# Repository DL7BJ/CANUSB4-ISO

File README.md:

CANUSB4-ISO 

Dieses Projekt basiert auf CANUSB4 vom MERG. Die Schaltung ist mit einer galvanischen Trennung zum USB Port erweitert. Der Code ist angepasst für MPLAB größer Version v6.25

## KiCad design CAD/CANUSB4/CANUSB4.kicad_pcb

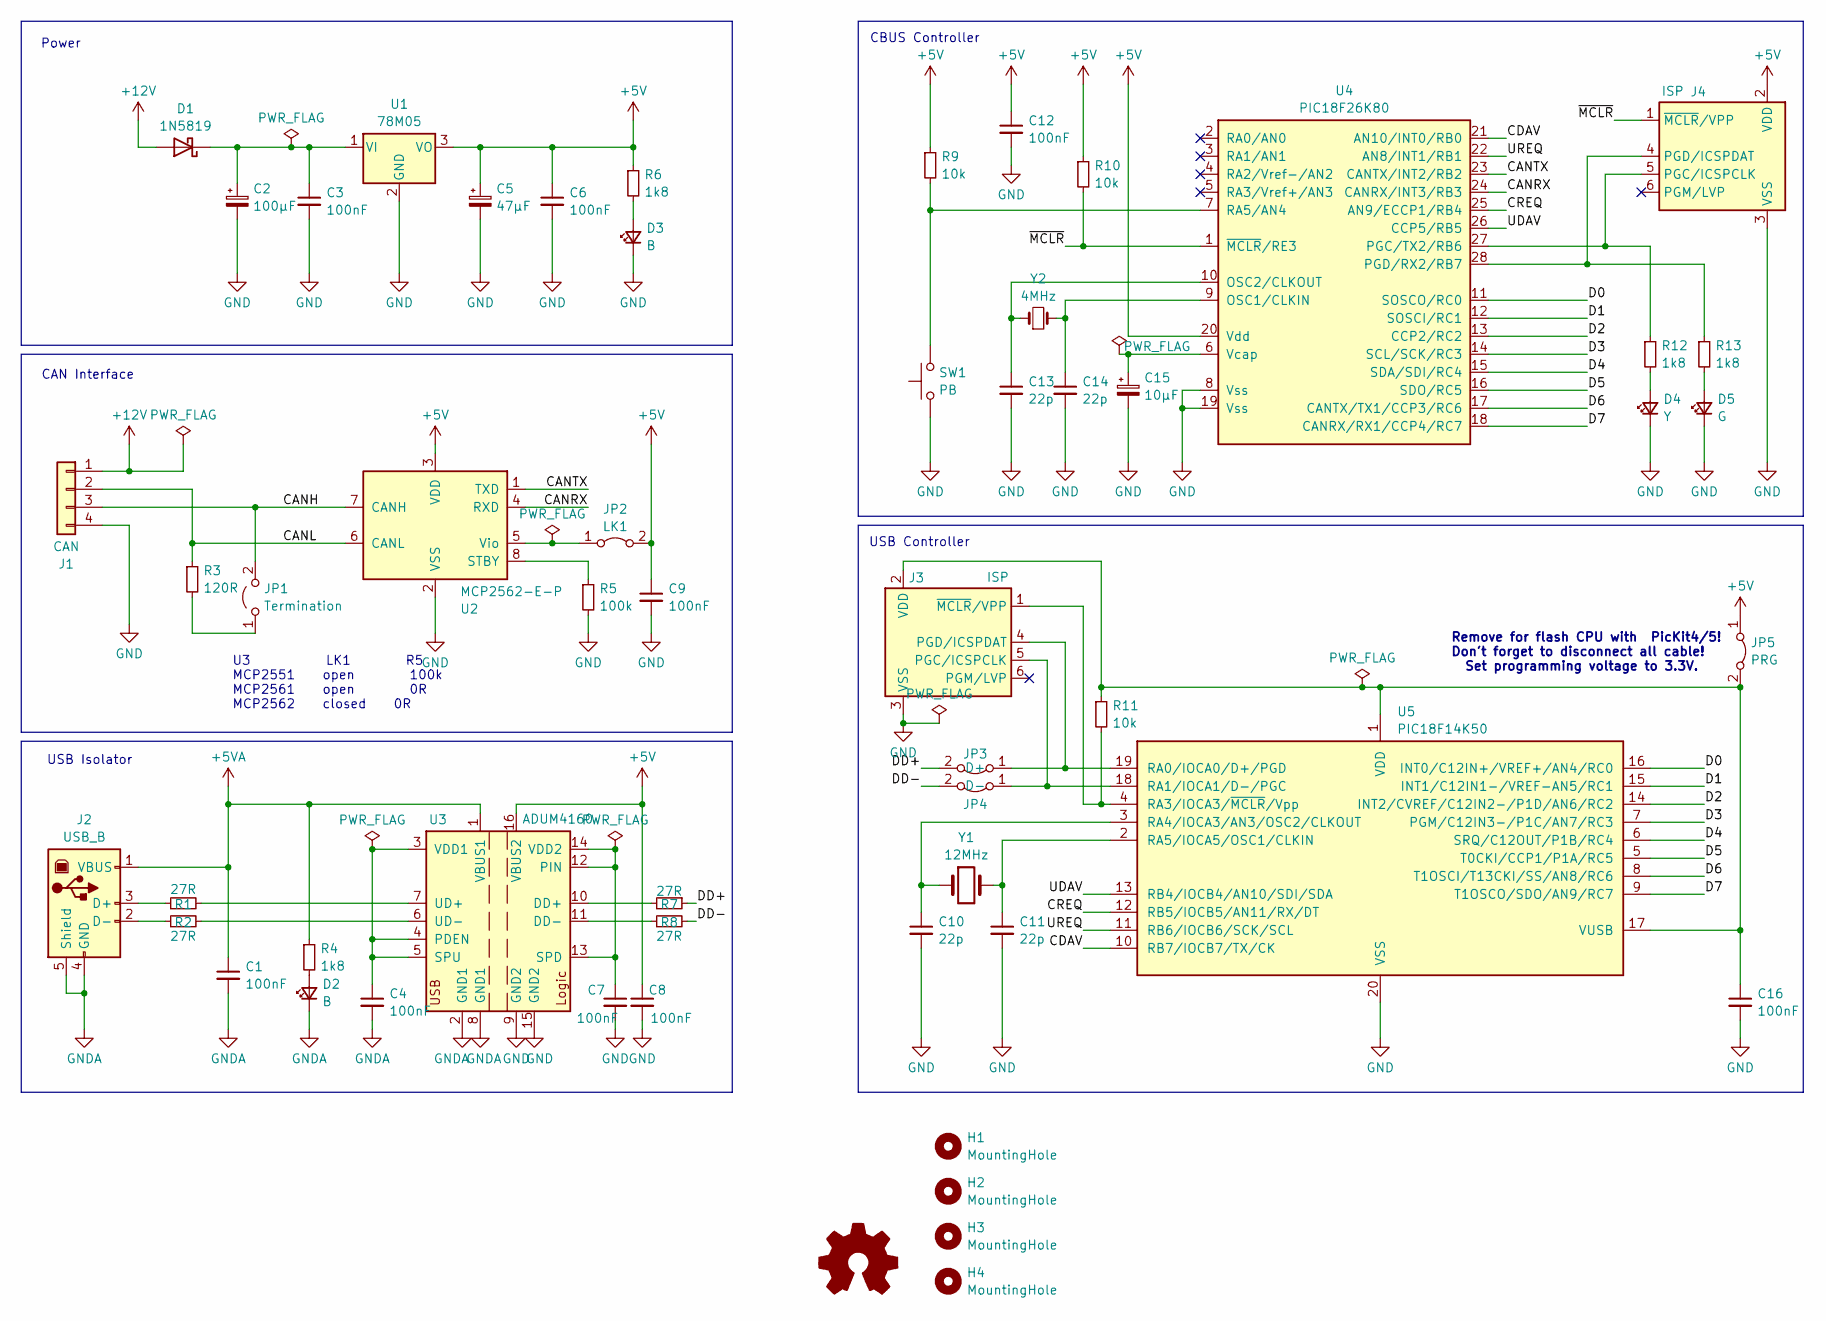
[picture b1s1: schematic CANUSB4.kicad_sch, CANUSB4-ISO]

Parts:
C1, C3, C4, C6, C7, C8, C9, C12, C16: 100nF; C_1206_3216Metric_Pad1.33x1.80mm_HandSolder
C2: 100µF; CP_Elec_8x10
C5: 47µF; CP_Elec_5x5.9
C10, C11, C13, C14: 22p; C_1206_3216Metric_Pad1.33x1.80mm_HandSolder
C15: 10µF; CP_Elec_4x5.3
D1: 1N5819; D_DO-41_SOD81_P10.16mm_Horizontal
D2, D3: B; LED_D3.0mm
D4: Y; LED_D3.0mm
D5: G; LED_D3.0mm
H1, H2, H3, H4: MountingHole; MountingHole_3.5mm
J1: CAN; PhoenixContact_MC_1,5_4-G-3.5_1x04_P3.50mm_Horizontal
J2: USB_B; USB_B_OST_USB-B1HSxx_Horizontal
J3, J4: ISP; PinHeader_1x06_P2.54mm_Vertical
JP1: Termination; PinSocket_1x02_P2.54mm_Vertical
JP2: LK1; PinSocket_1x02_P2.54mm_Vertical
JP3: D+; PinSocket_1x02_P2.54mm_Vertical
JP4: D-; PinSocket_1x02_P2.54mm_Vertical
JP5: PRG; PinSocket_1x02_P2.54mm_Vertical
R1, R2: 27R; R_1206_3216Metric_Pad1.30x1.75mm_HandSolder
R3: 120R; R_1206_3216Metric_Pad1.30x1.75mm_HandSolder
R4, R6, R12, R13: 1k8; R_1206_3216Metric_Pad1.30x1.75mm_HandSolder
R5: 100k; R_1206_3216Metric_Pad1.30x1.75mm_HandSolder
R7, R8: 27R; R_1206_3216Metric
R9, R10, R11: 10k; R_1206_3216Metric_Pad1.30x1.75mm_HandSolder
SW1: PB; SW_Tactile_SPST_Angled_PTS645Vx58-2LFS
U1: 78M05; TO-252-3_TabPin2
U2: MCP2562-E-P; DIP-8_W7.62mm
U3: ADUM4160; SOIC-16W_7.5x10.3mm_P1.27mm
U4: PIC18F26K80; DIP-28_W7.62mm_LongPads
U5: PIC18F14K50; DIP-20_W7.62mm
Y1: 12MHz; Crystal_HC49-4H_Vertical
Y2: 4MHz; Crystal_HC49-4H_Vertical

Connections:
+5V: C5.1, C6.1, C8.1, C9.1, C12.1, J4.2 (VDD), JP2.2 (B), JP5.1 (A), R6.1, R9.1, R10.1, U1.3 (VO), U2.3 (VDD), U3.16 (VBUS2), U4.20 (Vdd)
+5VA: C1.1, J2.1 (VBUS), R4.1, U3.1 (VBUS1)
+12V: D1.2 (A), J1.1
/CANH: J1.3, JP1.2 (B), U2.7 (CANH)
/CANL: J1.2, R3.1, U2.6 (CANL)
/CANRX: U2.4 (RXD), U4.24 (CANRX/INT3/RB3)
/CANTX: U2.1 (TXD), U4.23 (CANTX/INT2/RB2)
/CDAV: U4.21 (AN10/INT0/RB0), U5.10 (RB7/IOCB7/TX/CK)
/CREQ: U4.25 (AN9/ECCP1/RB4), U5.12 (RB5/IOCB5/AN11/RX/DT)
/D0: U4.11 (SOSCO/RC0), U5.16 (INT0/C12IN+/VREF+/AN4/RC0)
/D1: U4.12 (SOSCI/RC1), U5.15 (INT1/C12IN1-/VREF-AN5/RC1)
/D2: U4.13 (CCP2/RC2), U5.14 (INT2/CVREF/C12IN2-/P1D/AN6/RC2)
/D3: U4.14 (SCL/SCK/RC3), U5.7 (PGM/C12IN3-/P1C/AN7/RC3)
/D4: U4.15 (SDA/SDI/RC4), U5.6 (SRQ/C12OUT/P1B/RC4)
/D5: U4.16 (SDO/RC5), U5.5 (T0CKI/CCP1/P1A/RC5)
/D6: U4.17 (CANTX/TX1/CCP3/RC6), U5.8 (T1OSCI/T13CKI/SS/AN8/RC6)
/D7: U4.18 (CANRX/RX1/CCP4/RC7), U5.9 (T1OSCO/SDO/AN9/RC7)
/DD+: JP3.2 (B), R7.1
/DD-: JP4.2 (B), R8.2
/UDAV: U4.26 (CCP5/RB5), U5.13 (RB4/IOCB4/AN10/SDI/SDA)
/UREQ: U4.22 (AN8/INT1/RB1), U5.11 (RB6/IOCB6/SCK/SCL)
/~MCLR: J4.1 (~MCLR/VPP), R10.2, U4.1 (~MCLR/RE3)
GND: C2.2, C3.2, C5.2, C6.2, C7.2, C8.2, C9.2, C10.2, C11.2, C12.2, C13.2, C14.2, C15.2, C16.2, D3.1 (K), D4.1 (K), D5.1 (K), J1.4, J3.3 (VSS), J4.3 (VSS), R5.2, SW1.1, U1.2 (GND), U2.2 (VSS), U3.9 (GND2), U3.15 (GND2), U4.8 (Vss), U4.19 (Vss), U5.20 (VSS)
GNDA: C1.2, C4.2, D2.1 (K), J2.4 (GND), J2.5 (Shield), U3.2 (GND1), U3.8 (GND1)
unnamed: C2.1, C3.1, D1.1 (K), U1.1 (VI)
unnamed: D2.2 (A), R4.2
unnamed: D3.2 (A), R6.2
unnamed: D4.2 (A), R12.2
unnamed: D5.2 (A), R13.2
unnamed: J2.3 (D+), R1.1
unnamed: J2.2 (D-), R2.1
unnamed: J3.5 (PGC/ICSPCLK), JP4.1 (A), U5.18 (RA1/IOCA1/D-/PGC)
unnamed: J3.4 (PGD/ICSPDAT), JP3.1 (A), U5.19 (RA0/IOCA0/D+/PGD)
unnamed: C16.1, J3.2 (VDD), JP5.2 (B), R11.1, U5.1 (VDD), U5.17 (VUSB)
unnamed: J3.1 (~MCLR/VPP), R11.2, U5.4 (RA3/IOCA3/~MCLR/Vpp)
unnamed: J4.5 (PGC/ICSPCLK), R12.1, U4.27 (PGC/TX2/RB6)
unnamed: J4.4 (PGD/ICSPDAT), R13.1, U4.28 (PGD/RX2/RB7)
unnamed: JP1.1 (A), R3.2
unnamed: JP2.1 (A), U2.5 (Vio)
unnamed: R5.1, U2.8 (STBY)
unnamed: R7.2, U3.10 (DD+)
unnamed: R8.1, U3.11 (DD-)
unnamed: C4.1, U3.3 (VDD1), U3.4 (PDEN), U3.5 (SPU)
unnamed: C7.1, U3.12 (PIN), U3.13 (SPD), U3.14 (VDD2)
unnamed: R1.2, U3.7 (UD+)
unnamed: R2.2, U3.6 (UD-)
unnamed: C14.1, U4.9 (OSC1/CLKIN), Y2.2
unnamed: C13.1, U4.10 (OSC2/CLKOUT), Y2.1
unnamed: R9.2, SW1.2, U4.7 (RA5/AN4)
unnamed: C15.1, U4.6 (Vcap)
unnamed: C10.1, U5.3 (RA4/IOCA3/AN3/OSC2/CLKOUT), Y1.1
unnamed: C11.1, U5.2 (RA5/IOCA5/OSC1/CLKIN), Y1.2

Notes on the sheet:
Remove for flash CPU with PicKit4/5! Don't forget to disconnect all cable! Set programming voltage to 3.3V.
U3 LK1 R5 MCP2551 open 100k MCP2561 open 0R MCP2562 closed 0R
CBUS Controller
USB Isolator
Power
CAN Interface
USB Controller

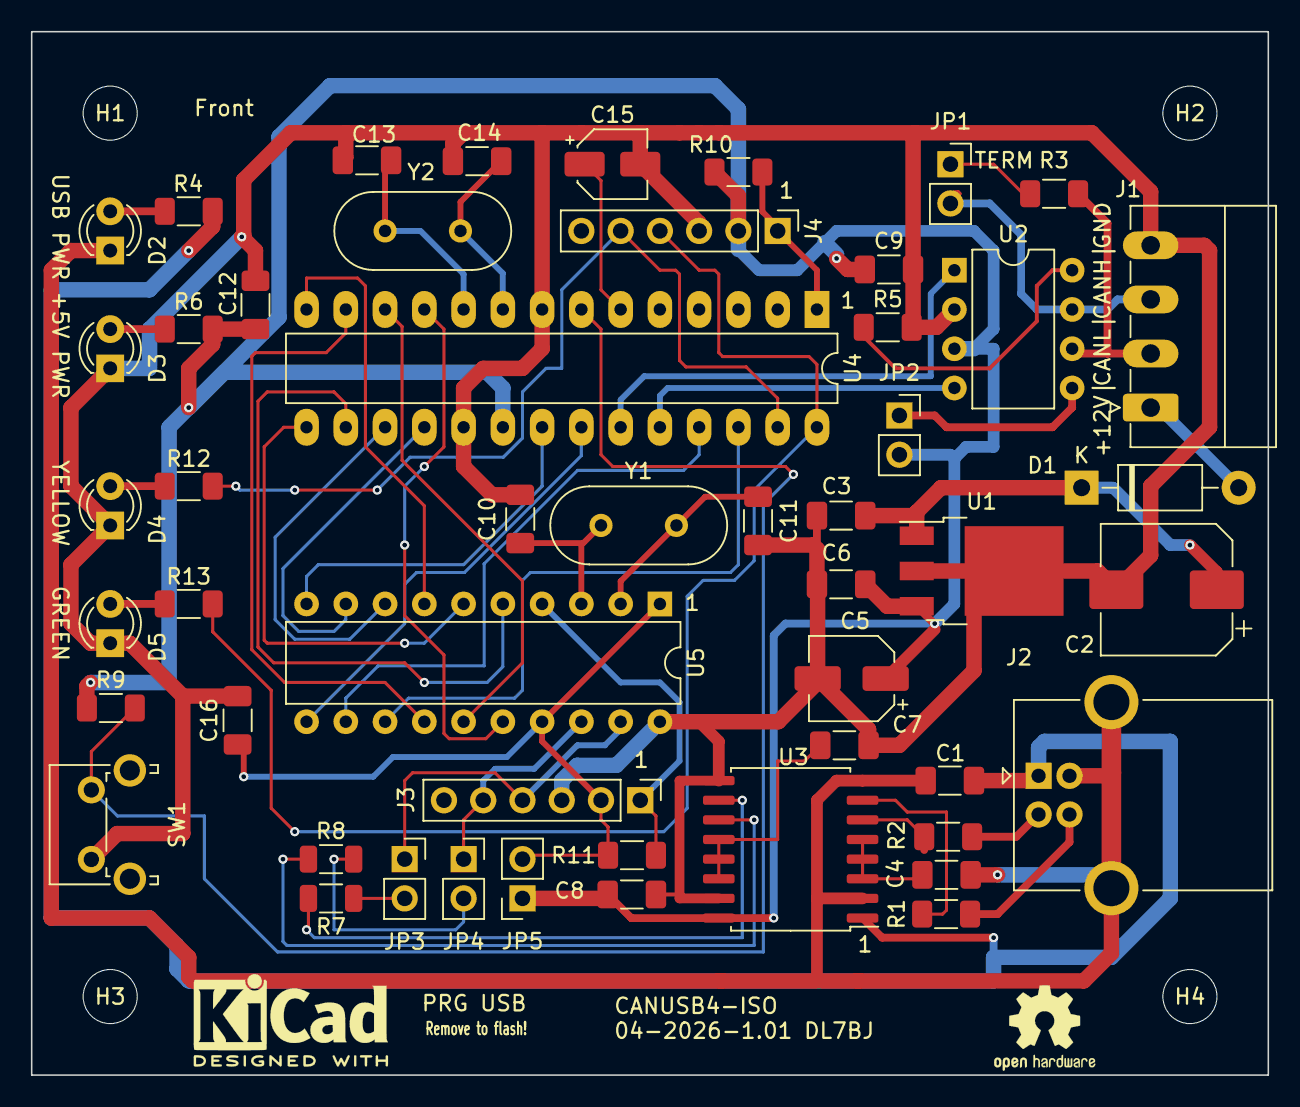
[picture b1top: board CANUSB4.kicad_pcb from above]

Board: 2 copper layers, 80.0 x 67.5 mm, 55 parts (0 on the bottom side), 52 nets.

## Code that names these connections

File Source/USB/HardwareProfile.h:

/*------------------------------------------------------------------------------
; PICFT245
;
; FTDI FT245 replacement in a POC18F14K50 (C) SPROG DCC 2012
;	web:	http://www.sprog-dcc.co.uk
;	e-mail:	sprog@sprog-dcc.co.uk
;-----------------------------------------------------------------------------*/

#ifndef HARDWARE_PROFILE_H
#define HARDWARE_PROFILE_H

/*
 18F14K50 MERG CAN USB 4 pinout

           |----------------------------|
 Power     |1  Vdd                VSS 20| Power
 Xtal      |2  RA5/OSC1        D+/RA0 19| USB
 Xtal      |3  RA4/OSC2        D-/RA1 18| USB
 MCLR      |4  RA3/MCLR          VUSB 17| USB
 D5        |5  RC5/CCP1       AN4/RC0 16| D0
 D4        |6  RC4/P1B        AN5/RC1 15| D1
 D3        |7  RC3/AN7        AN6/RC2 14| D2
 D6        |8  RC6/AN8       AN10/RB4 13| UDAV
 D7        |9  RC7/AN9    RX/AN11/RB5 12| CREQ
 CDAV      |10 RB7/TX             RB6 11| UREQ
           |----------------------------|
*/

//
// Port C
#define DATA_PORT       PORTC
#define DATA_PORTbits   PORTCbits

// Default to inputs
#define PORTC_DDR       0b11111111
#define PORTC_INIT      0b00000000

//
// Port B
//
#define UDAV            RB4   // 
#define CREQ            RB5   // 
#define UREQ            RB6   // 
#define CDAV            RB7   // 

// 
#define PORTB_DDR       0b11000000
#define PORTB_INIT      0b00000000

//
// Port A
//
// USB D+               RA0   // reserved
// USB D-               RA1   // reserved
// [VUSB]               RA2   // reserved
// MCLR                 RA3   // reserved
// OSC2                 RA4   // reserved
// OSC1                 RA5   // reserved

#define PORTA_DDR	0xFF
#define PORTA_INIT	0x00

//
// From low pin count hardware profile
//
    /*******************************************************************/
    /******** USB stack hardware selection options *********************/
    /*******************************************************************/
    //This section is the set of definitions required by the MCHPFSUSB
    //  framework.  These definitions tell the firmware what mode it is
    //  running in, and where it can find the results to some information
    //  that the stack needs.
    //These definitions are required by every application developed with
    //  this revision of the MCHPFSUSB framework.  Please review each
    //  option carefully and determine which options are desired/required
    //  for your application.

    #define self_power          1

    #define USB_BUS_SENSE       1

    /*******************************************************************/
    /******** Application specific definitions *************************/
    /*******************************************************************/

    /** Board definition ***********************************************/
    //These defintions will tell the main() function which board is
    //  currently selected.  This will allow the application to add
    //  the correct configuration bits as wells use the correct
    //  initialization functions for the board.  These defitions are only
    //  required in the stack provided demos.  They are not required in
    //  final application design.

    #define CLOCK_FREQ 48000000
    #define GetSystemClock() CLOCK_FREQ

    /** LED ************************************************************/
    #define mLED_1              
    #define mLED_2              

    #define mGetLED_1()         
    #define mGetLED_2()         

    #define mLED_1_On()         
    #define mLED_2_On()         

    #define mLED_1_Off()        
    #define mLED_2_Off()        
    
    #define mLED_1_Toggle()     
    #define mLED_2_Toggle()     

#endif  //HARDWARE_PROFILE_H

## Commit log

2026-01-23 KiCAD Daten, Schaltplan & Platine erstellt
2026-01-23 Add README.md
2026-01-23 BOM hinzugefügt
2026-01-24 Originalquelltexte unter Source hinzugefügt
2026-04-10 New CAD data created with KiCAD 10.0
2026-04-10 Correct some files
2026-04-10 Fix typo in README.md for MPLAB version
2026-04-10 Add GPL v3 license
    Add the GNU General Public License version 3 to the project.
2026-04-10 Add pdf files, CAD files
